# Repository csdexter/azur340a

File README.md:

#Cambridge Audio Azur 340A "Patches"#

(C) 2014 Radu - Eosif Mihailescu <radu.mihailescu@linux360.ro>

All files in this repository are licensed under the
**GNU Generic Public License v3**, a copy of whose text can be accessed
 [here](http://www.gnu.org/licenses/gpl.html).

This repository contains [EDA](http://en.wikipedia.org/wiki/Electronic_design_automation) source files for all of the boards in this project in CadSoft Eagle 7 format. Only the `.SCH` (schematic) and `.BRD` (board) files are provided as all data needed for manufacturing can easily be derived from the former. No guarantee is made as to which minor version of Eagle was used to save the file, but it *may* be the latest at the time of this writing.

The board description files *may* contain routing information or be supplied unrouted. In the former case, the routing artwork *may* have been generated by either Eagle's internal autorouter or [FreeRouting](http://www.freerouting.net/). A 25mil routing grid and 10/10mil trace/space settings will have been used in both cases.

All files included here are compatible with the free version of Eagle (i.e. describe PCBs having no more than 2 layers and measuring no more than 10cm by 8cm each).

Git tags will be used to mark specific revisions that were actually manufactured so that a correspondence between the evolution of the sources and the status of physical by-products can be maintained.

##WARNING##
*Unless and until explictily noted otherwise, the engineering materials here are laboratory quality and neither intended for manufacturing in production quantities nor for distribution (e.g. as kits) to end-users. The design data here does not explicitly follow any widely-accepted safety/security/EMI regulation or standard, therefore any manufacturing and/or usage in connection with live equipment is entirely at your own risk.*

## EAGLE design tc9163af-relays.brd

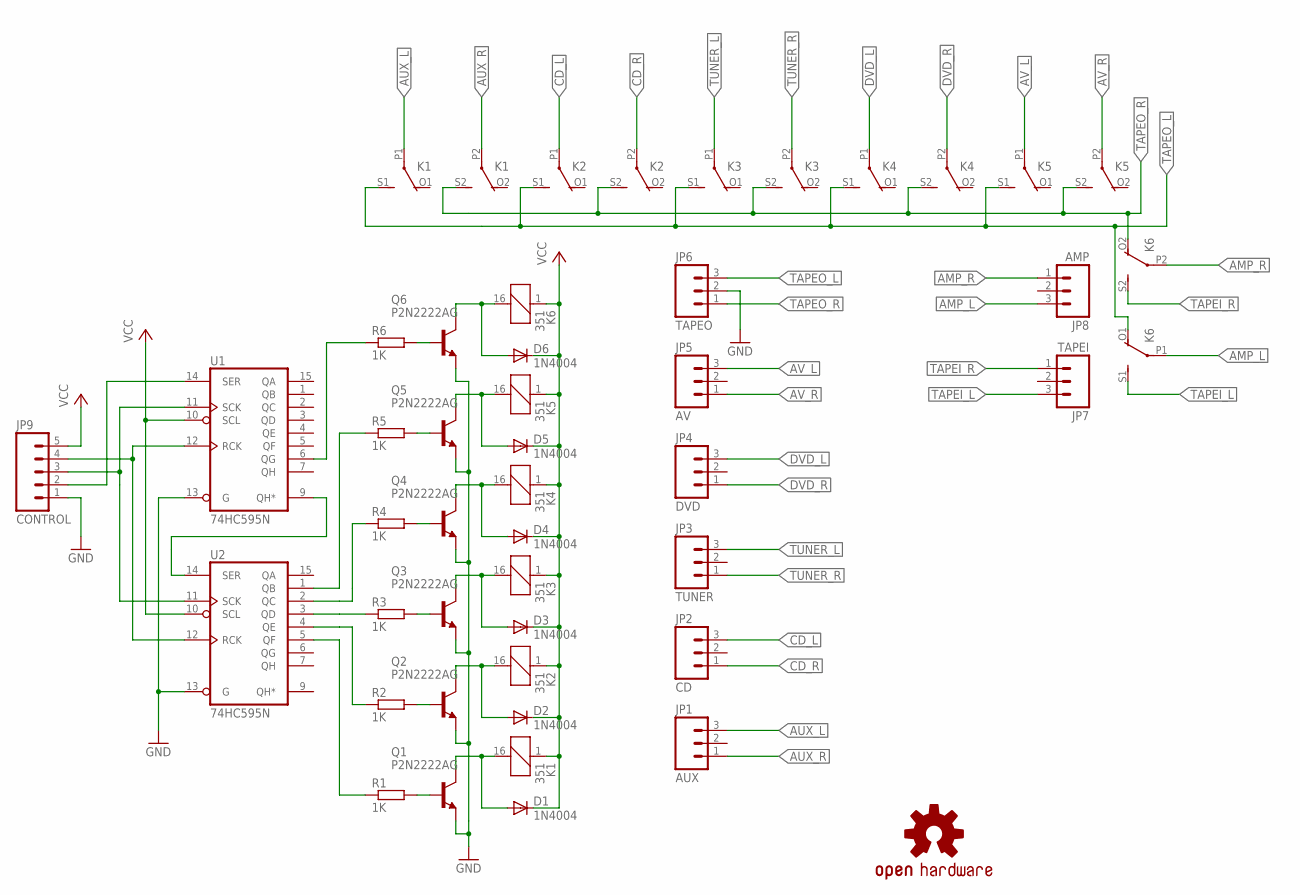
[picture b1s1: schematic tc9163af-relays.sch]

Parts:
D1, D2, D3, D4, D5, D6: 1N4004; DO41-10
JP1: AUX; 1X03
JP2: CD; 1X03
JP3: TUNER; 1X03
JP4: DVD; 1X03
JP5: AV; 1X03
JP6: TAPEO; 1X03
JP7: TAPEI; 1X03
JP8: AMP; 1X03
JP9: CONTROL; 1X05
K1, K2, K3, K4, K5, K6: 351
LOGO1: OSHW-LOGOL; OSHW-LOGO-L
Q1, Q2, Q3, Q4, Q5, Q6: P2N2222AG; TO92-EBC
R1, R2, R3, R4, R5, R6: 1K; 0207/10
U1, U2: 74HC595N; DIL16

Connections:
AMP_L: JP8.3, K6.P1
AMP_R: JP8.1, K6.P2
AUX_L: JP1.3, K1.P1
AUX_R: JP1.1, K1.P2
AV_L: JP5.3, K5.P1
AV_R: JP5.1, K5.P2
CD_L: JP2.3, K2.P1
CD_R: JP2.1, K2.P2
CLOCK: JP9.3, U1.11 (SCK), U2.11 (SCK)
DATA: JP9.2, U1.14 (SER)
DVD_L: JP4.3, K4.P1
DVD_R: JP4.1, K4.P2
GND: JP6.2, JP9.1, Q1.E, Q2.E, Q3.E, Q4.E, Q5.E, Q6.E, U1.8 (GND), U1.13 (G), U2.8 (GND), U2.13 (G)
unnamed: U1.9 (QH*), U2.14 (SER)
unnamed: R4.1, U2.2 (QC)
unnamed: R5.1, U2.1 (QB)
unnamed: R1.1, U2.5 (QF)
unnamed: R2.1, U2.4 (QE)
unnamed: R3.1, U2.3 (QD)
unnamed: R6.1, U1.6 (QG)
unnamed: Q1.B, R1.2
unnamed: D1.A, K1.16 (2), Q1.C
unnamed: Q5.B, R5.2
unnamed: Q2.B, R2.2
unnamed: D2.A, K2.16 (2), Q2.C
unnamed: Q6.B, R6.2
unnamed: D6.A, K6.16 (2), Q6.C
unnamed: Q3.B, R3.2
unnamed: D3.A, K3.16 (2), Q3.C
unnamed: Q4.B, R4.2
unnamed: D4.A, K4.16 (2), Q4.C
unnamed: D5.A, K5.16 (2), Q5.C
STROBE: JP9.4, U1.12 (RCK), U2.12 (RCK)
TAPEI_L: JP7.3, K6.S1 (S)
TAPEI_R: JP7.1, K6.S2 (S)
TAPEO_L: JP6.3, K1.S1 (S), K2.S1 (S), K3.S1 (S), K4.S1 (S), K5.S1 (S), K6.O1 (O)
TAPEO_R: JP6.1, K1.S2 (S), K2.S2 (S), K3.S2 (S), K4.S2 (S), K5.S2 (S), K6.O2 (O)
TUNER_L: JP3.3, K3.P1
TUNER_R: JP3.1, K3.P2
VCC: D1.C, D2.C, D3.C, D4.C, D5.C, D6.C, JP9.5, K1.1, K2.1, K3.1, K4.1, K5.1, K6.1, U1.10 (SCL), U1.16 (VCC), U2.10 (SCL), U2.16 (VCC)

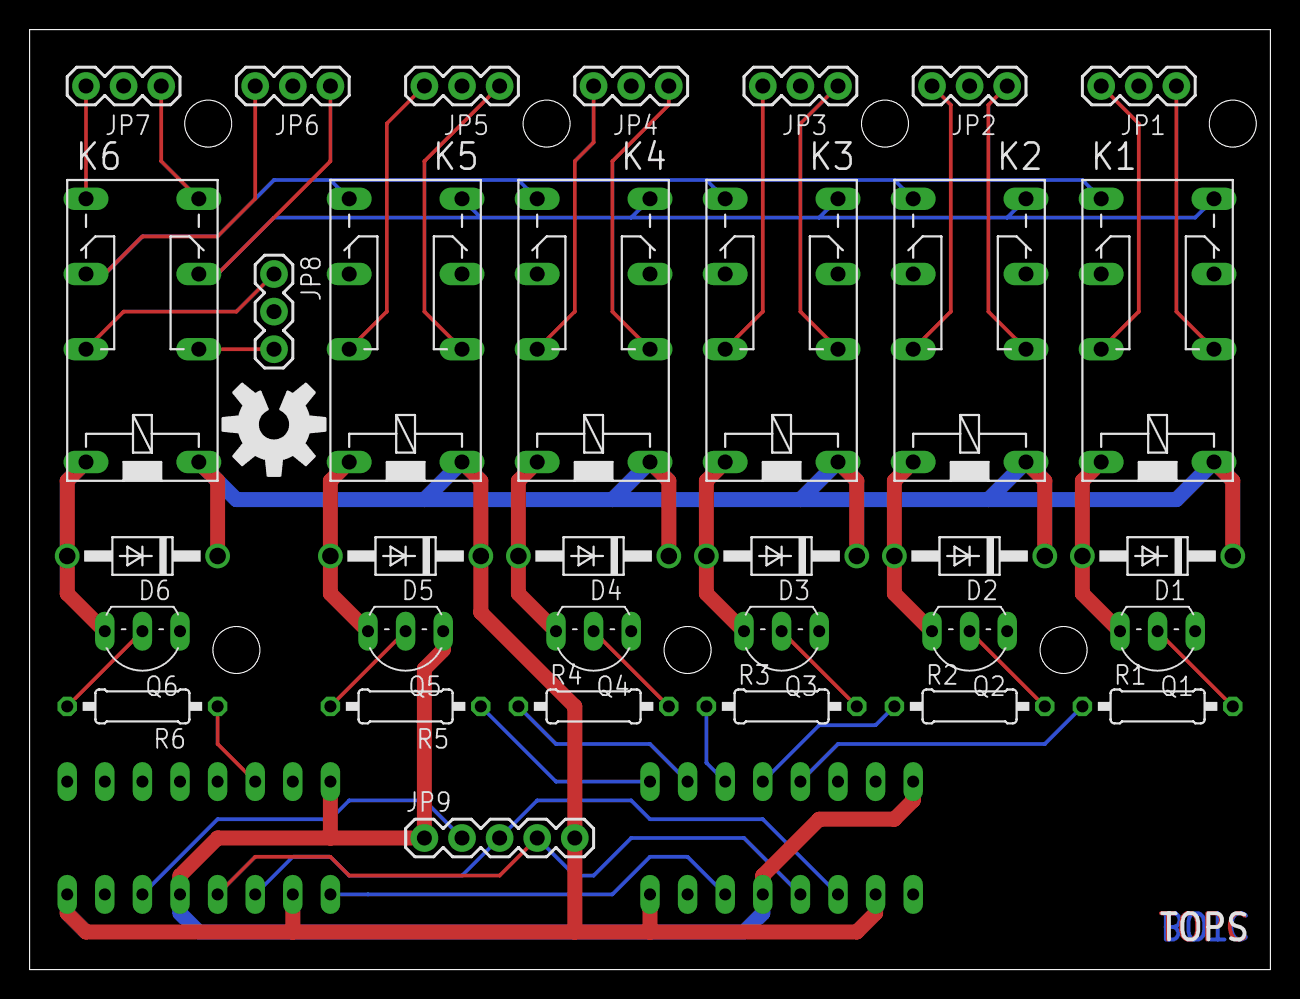
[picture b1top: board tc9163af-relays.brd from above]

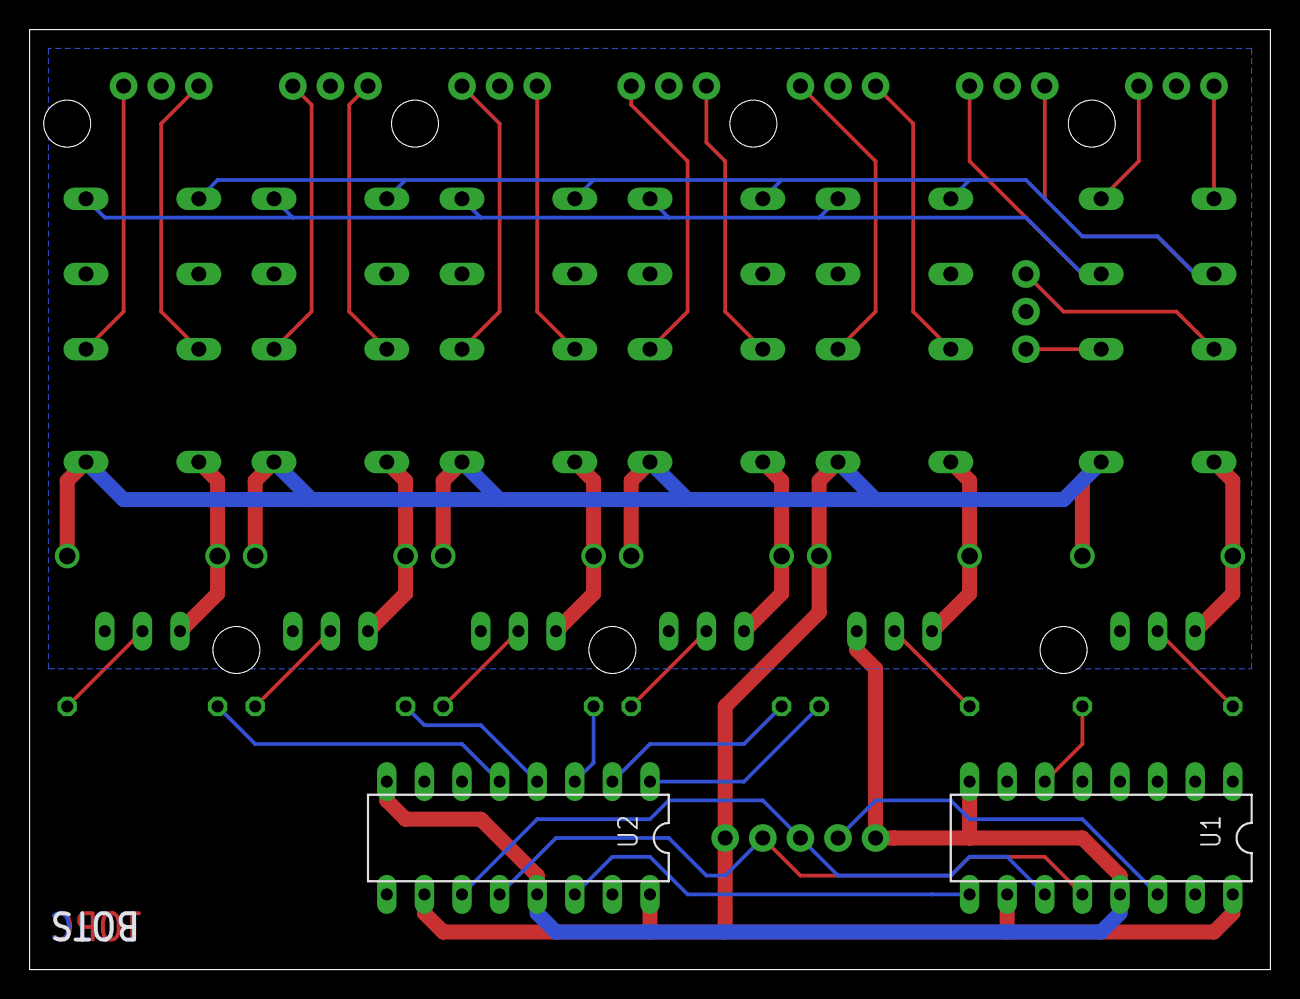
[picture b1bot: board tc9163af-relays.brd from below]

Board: 2 copper layers, 83.8 x 63.5 mm, 36 parts (2 on the bottom side), 40 nets.

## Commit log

2014-08-04 Initial commit: - Toshiba TC9163A(F) emulator board, does away with crappy input switcher going tits-up every 6 months

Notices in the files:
parts and their libraries:
SparkFun-Connectors: Licensing: Creative Commons ShareAlike 4.0 International - https://creativecommons.org/licenses/by-sa/4.0
